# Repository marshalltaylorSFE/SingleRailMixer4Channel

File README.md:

Single-rail 4 channel mixer
=====================================
Design files for building a mixer suitable for mixing straight off the analog out pins of your favorite Arduino variant.

Repository Contents
-------------------

* **/Layout** - Simple eagle layout intended for toner transfer method (no drills)
* **/Simulation** - LTSpice simulations of the various circuits

Version History
---------------
* [V_0.2.0](https://github.com/marshalltaylorSFE/SingleRailMixer4Channel/tree/V_0.2.0) - Proto Hardware created
* [V_0.1.0](https://github.com/marshalltaylorSFE/SingleRailMixer4Channel/tree/V_0.1.0) - Simulation

License Information
-------------------
The hardware is released under [Creative Commons ShareAlike 4.0 International](https://creativecommons.org/licenses/by-sa/4.0/).
The code is beerware; if you see me at the local, and you've found our code helpful, please buy us a round!

Distributed as-is; no warranty is given.

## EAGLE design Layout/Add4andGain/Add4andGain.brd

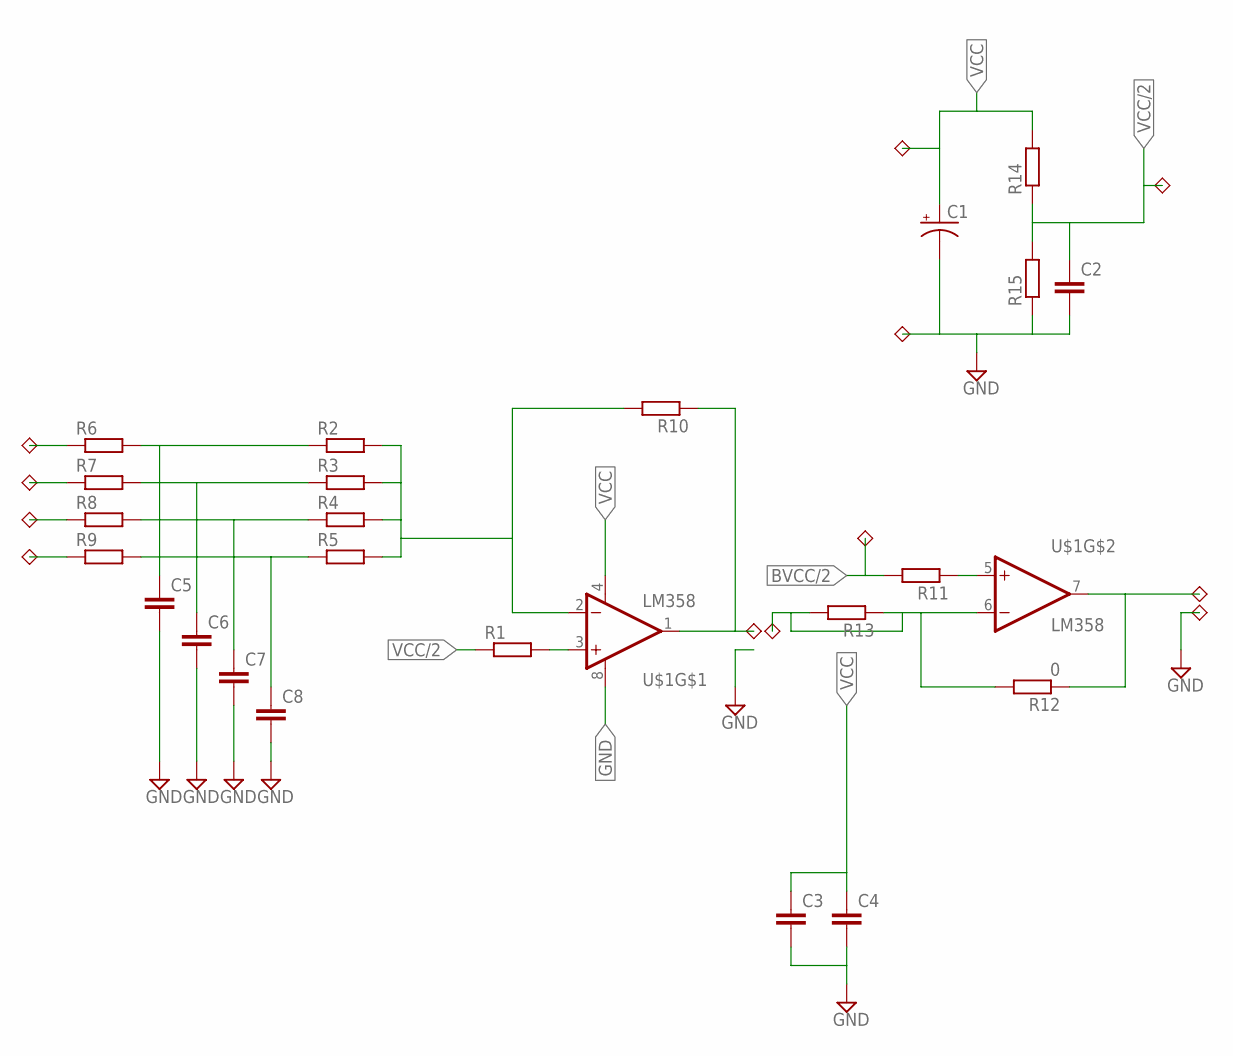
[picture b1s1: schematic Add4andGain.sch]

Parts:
C1: CPOL-USSMCE; SMC_E
C2, C3, C4, C5, C6, C7, C8: C-EUC0805; C0805
R1, R2, R3, R4, R5, R6, R7, R8, R9, R10, R11, R13, R14, R15: R-EU_R0603; R0603
R12: 0; R0603
U$1: LM358; SO08
U$2, U$3, U$4, U$5, U$6, U$7, U$8, U$9, U$10, U$12, U$15, U$16: 1PIN_SM; THUMBNAIL_SM

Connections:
AIN+: R1.2, U$1.3 (+IN)
AIN-: R2.2, R3.2, R4.2, R5.2, R10.2, U$1.2 (-IN)
BIN+: R11.1, U$1.5 (+IN)
BIN-: R12.2, R13.1, R13.2, U$1.6 (-IN), U$9.P$1
BVCC/2: R11.2, U$6.P$1
GND: C1.-, C2.2, C3.2, C4.2, C5.2, C6.2, C7.2, C8.2, R15.1, U$1.8 (V+), U$7.P$1, U$16.P$1
unnamed: R6.1, U$2.P$1
unnamed: R12.1, U$1.7 (OUT), U$15.P$1
unnamed: R7.1, U$3.P$1
unnamed: R8.1, U$4.P$1
unnamed: R9.1, U$5.P$1
unnamed: C5.1, R2.1, R6.2
unnamed: C6.1, R3.1, R7.2
unnamed: C7.1, R4.1, R8.2
unnamed: C8.1, R5.1, R9.2
unnamed: R10.1, U$1.1 (OUT), U$8.P$1
VCC: C1.+, C3.1, C4.1, R14.2, U$1.4 (V-), U$12.P$1
VCC/2: C2.1, R1.1, R14.1, R15.2, U$10.P$1

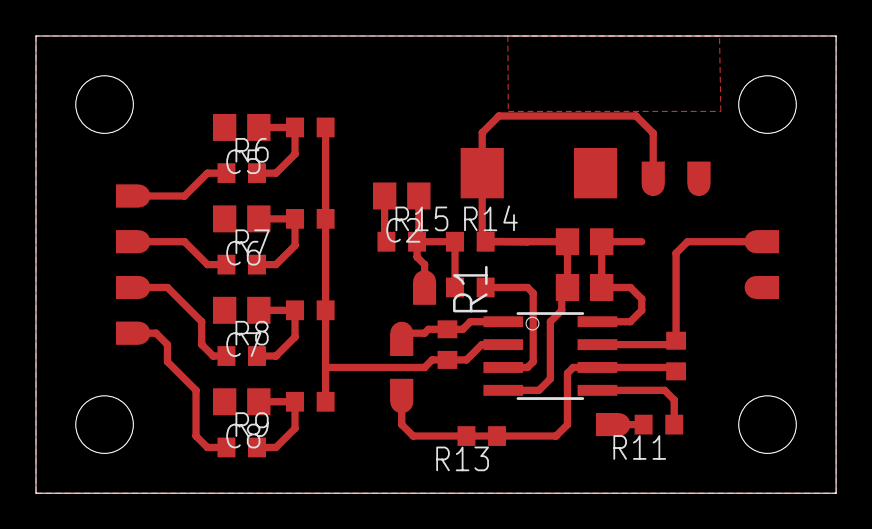
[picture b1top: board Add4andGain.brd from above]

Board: 2 copper layers, 44.5 x 25.4 mm, 36 parts (0 on the bottom side), 18 nets.

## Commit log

2015-04-26 Simulation done
2015-04-26 added tag
2015-04-27 Proto created
